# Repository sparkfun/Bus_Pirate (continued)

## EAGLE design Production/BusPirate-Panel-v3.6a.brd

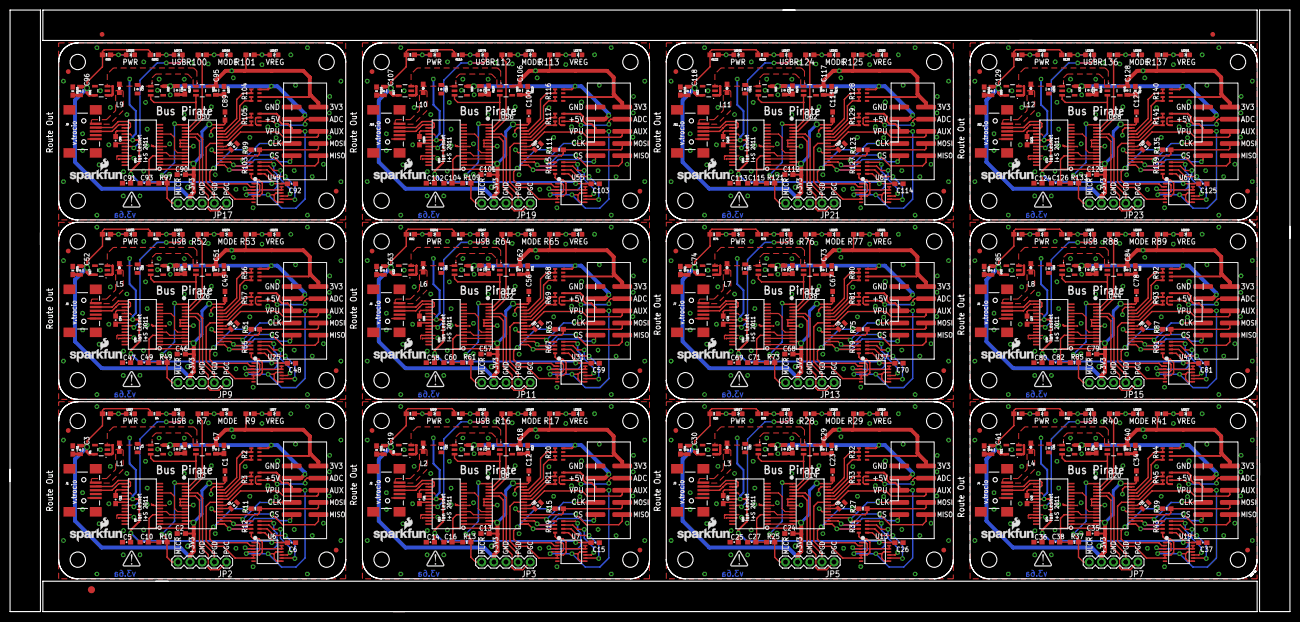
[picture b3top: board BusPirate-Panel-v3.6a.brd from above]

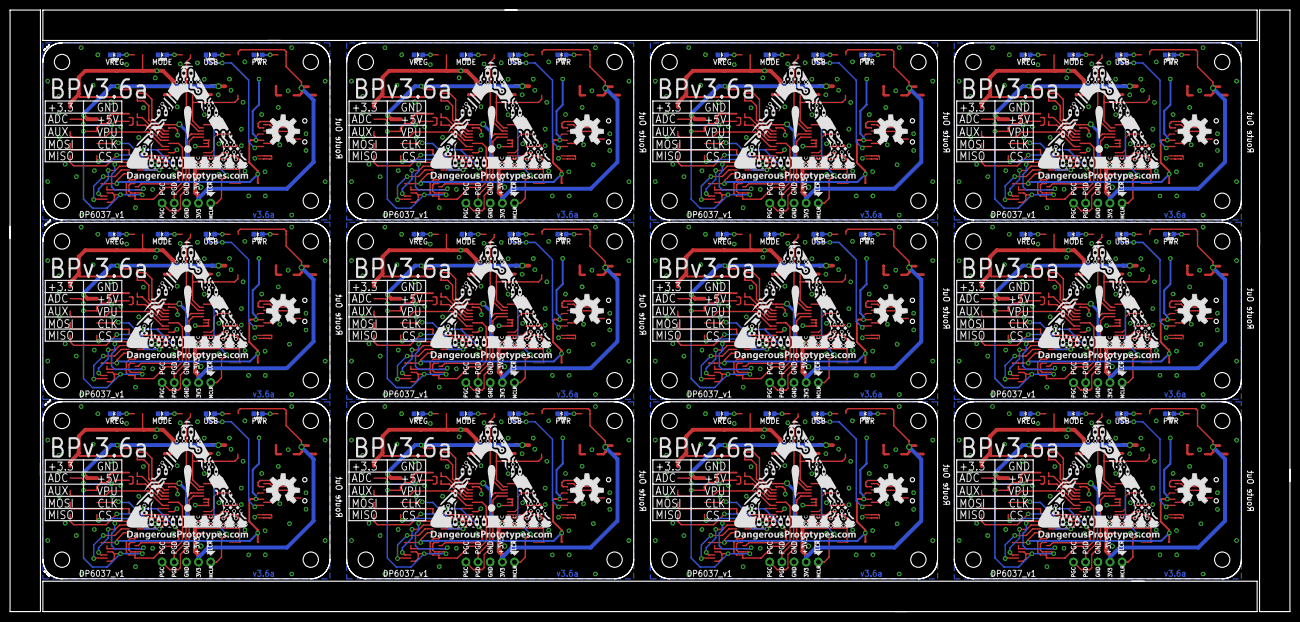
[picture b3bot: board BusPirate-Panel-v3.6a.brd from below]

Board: 2 copper layers, 267.5 x 125.7 mm, 579 parts (72 on the bottom side), 516 nets.

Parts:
C1, C2, C5, C6, C10, C11, C12, C13, C14, C15, C16, C21, C23, C24, C25, C26, C27, C32, C34, C35, C36, C37, C38, C43, C45, C46, C47, C48, C49, C54, C56, C57, C58, C59, C60, C65, C67, C68, C69, C70, C71, C76, C78, C79, C80, C81, C82, C87, C89, C90, C91, C92, C93, C98, C100, C101, C102, C103, C104, C109, C111, C112, C113, C114, C115, C120, C122, C123, C124, C125, C126, C131: 0.1uF; 0603-CAP
C3, C4, C7, C8, C9, C17, C18, C19, C20, C22, C28, C29, C30, C31, C33, C39, C40, C41, C42, C44, C50, C51, C52, C53, C55, C61, C62, C63, C64, C66, C72, C73, C74, C75, C77, C83, C84, C85, C86, C88, C94, C95, C96, C97, C99, C105, C106, C107, C108, C110, C116, C117, C118, C119, C121, C127, C128, C129, C130, C132: 10uF; 0805-CAP
E$1: FIDUCIAL-1.5X3
E$7, E$8: FIDUCIAL-1X2
FID1, FID2, FID3, FID4, FID5, FID6, FID7, FID8, FID9, FID10, FID11, FID12, FID13, FID14, FID15, FID16, FID17, FID18, FID19, FID20, FID21, FID22, FID23, FID24: FIDUCIAL1X2; FIDUCIAL-1X2
J1, J2, J3, J4, J5, J6, J7, J8, J9, J10, J11, J12: USB-MINIB-5PIN; USB-MINIB
JP1, JP4, JP6, JP8, JP10, JP12, JP14, JP16, JP18, JP20, JP22, JP24: 2X5-SHROUDED_SMD
JP2, JP3, JP5, JP7, JP9, JP11, JP13, JP15, JP17, JP19, JP21, JP23: 1X05
L1, L2, L3, L4, L5, L6, L7, L8, L9, L10, L11, L12: 1A Ferrite; 0603
LED1, LED3, LED5, LED7, LED9, LED10, LED11, LED15, LED17, LED18, LED19, LED23, LED25, LED26, LED27, LED31, LED33, LED34, LED35, LED39, LED41, LED42, LED43, LED47, LED49, LED50, LED51, LED55, LED57, LED58, LED59, LED63, LED65, LED66, LED67, LED71, LED73, LED74, LED75, LED79, LED81, LED82, LED83, LED87, LED89, LED90, LED91, LED95: RED; LED-0603
LED2, LED4, LED6, LED8, LED12, LED13, LED14, LED16, LED20, LED21, LED22, LED24, LED28, LED29, LED30, LED32, LED36, LED37, LED38, LED40, LED44, LED45, LED46, LED48, LED52, LED53, LED54, LED56, LED60, LED61, LED62, LED64, LED68, LED69, LED70, LED72, LED76, LED77, LED78, LED80, LED84, LED85, LED86, LED88, LED92, LED93, LED94, LED96: DNP; LED-0603
LOGO1, LOGO4, LOGO6, LOGO8, LOGO10, LOGO12, LOGO14, LOGO16, LOGO18, LOGO20, LOGO22, LOGO24: OSHW-LOGOL; OSHW-LOGO-L
LOGO2, LOGO3, LOGO5, LOGO7, LOGO9, LOGO11, LOGO13, LOGO15, LOGO17, LOGO19, LOGO21, LOGO23: SFE_LOGO_NAME_FLAME.1_INCH; SFE_LOGO_NAME_FLAME_.1
PCB1, PCB2, PCB3, PCB4, PCB5, PCB6, PCB7, PCB8, PCB9, PCB10, PCB11, PCB12: PCB_DP_RECTANGLE-37X60; DP6037_V1
R1, R5, R8, R22, R23, R24, R34, R35, R36, R46, R47, R48, R58, R59, R60, R70, R71, R72, R82, R83, R84, R94, R95, R96, R106, R107, R108, R118, R119, R120, R130, R131, R132, R142, R143, R144: 0; 0603
R2, R3, R12, R19, R20, R21, R31, R32, R33, R43, R44, R45, R55, R56, R57, R67, R68, R69, R79, R80, R81, R91, R92, R93, R103, R104, R105, R115, R116, R117, R127, R128, R129, R139, R140, R141: 10k; 4XARRAY
R4, R6, R7, R9, R14, R16, R17, R18, R26, R28, R29, R30, R38, R40, R41, R42, R50, R52, R53, R54, R62, R64, R65, R66, R74, R76, R77, R78, R86, R88, R89, R90, R98, R100, R101, R102, R110, R112, R113, R114, R122, R124, R125, R126, R134, R136, R137, R138: 1K; 0603-RES
R10, R11, R13, R15, R25, R27, R37, R39, R49, R51, R61, R63, R73, R75, R85, R87, R97, R99, R109, R111, R121, R123, R133, R135: 2.0k; 0603-RES
U1, U2, U9, U10, U15, U16, U21, U22, U27, U28, U33, U34, U39, U40, U45, U46, U51, U52, U57, U58, U63, U64, U69, U70: MIC5205 3V3; SOT23-5
U3, U8, U14, U20, U26, U32, U38, U44, U50, U56, U62, U68: PIC24FJ64GA002; SSOP28
U4, U11, U17, U23, U29, U35, U41, U47, U53, U59, U65, U71: MIC5205 5V0; SOT23-5
U5, U12, U18, U24, U30, U36, U42, U48, U54, U60, U66, U72: FT232RL-BASICSSOP; SSOP28DB
U6, U7, U13, U19, U25, U31, U37, U43, U49, U55, U61, U67: 4066; TSSOP14
U$1, U$2, U$5, U$7, U$9, U$11, U$13, U$15, U$17, U$19, U$21, U$23: DP-LOGO
U$3, U$4, U$6, U$8, U$10, U$12, U$14, U$16, U$18, U$20, U$22, U$24: DP_LOGO_ART_1X1

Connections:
5V: C4.1, C5.1, C6.1, L1.2, R12.5, U1.1, U1.3, U2.1, U4.1, U5.20, U6.14
5V1: C14.1, C15.1, C22.1, L2.2, R19.5, U7.14, U9.1, U9.3, U10.1, U11.1, U12.20
5V2: C25.1, C26.1, C33.1, L3.2, R31.5, U13.14, U15.1, U15.3, U16.1, U17.1, U18.20
5V3: C36.1, C37.1, C44.1, L4.2, R43.5, U19.14, U21.1, U21.3, U22.1, U23.1, U24.20
5V4: C47.1, C48.1, C55.1, L5.2, R55.5, U25.14, U27.1, U27.3, U28.1, U29.1, U30.20
5V5: C58.1, C59.1, C66.1, L6.2, R67.5, U31.14, U33.1, U33.3, U34.1, U35.1, U36.20
5V6: C69.1, C70.1, C77.1, L7.2, R79.5, U37.14, U39.1, U39.3, U40.1, U41.1, U42.20
5V7: C80.1, C81.1, C88.1, L8.2, R91.5, U43.14, U45.1, U45.3, U46.1, U47.1, U48.20
5V8: C91.1, C92.1, C99.1, L9.2, R103.5, U49.14, U51.1, U51.3, U52.1, U53.1, U54.20
5V9: C102.1, C103.1, C110.1, L10.2, R115.5, U55.14, U57.1, U57.3, U58.1, U59.1, U60.20
5V10: C113.1, C114.1, C121.1, L11.2, R127.5, U61.14, U63.1, U63.3, U64.1, U65.1, U66.20
5V11: C124.1, C125.1, C132.1, L12.2, R139.5, U67.14, U69.1, U69.3, U70.1, U71.1, U72.20
!MCLR: JP2.5, R10.1, U3.1
!MCLR1: JP3.5, R13.1, U8.1
!MCLR2: JP5.5, R25.1, U14.1
!MCLR3: JP7.5, R37.1, U20.1
!MCLR4: JP9.5, R49.1, U26.1
!MCLR5: JP11.5, R61.1, U32.1
!MCLR6: JP13.5, R73.1, U38.1
!MCLR7: JP15.5, R85.1, U44.1
!MCLR8: JP17.5, R97.1, U50.1
!MCLR9: JP19.5, R109.1, U56.1
!MCLR10: JP21.5, R121.1, U62.1
!MCLR11: JP23.5, R133.1, U68.1
$N1: J2.VBUS, L2.1
$N2: J3.VBUS, L3.1
$N3: J4.VBUS, L4.1
$N4: J5.VBUS, L5.1
$N5: J6.VBUS, L6.1
$N6: J7.VBUS, L7.1
$N7: J8.VBUS, L8.1
$N8: J9.VBUS, L9.1
$N9: J10.VBUS, L10.1
$N10: J11.VBUS, L11.1
$N11: J12.VBUS, L12.1
$N26: J1.VBUS, L1.1
ADC: JP1.4, R3.6
ADC1: R3.3, R3.4, U3.23
ADC2: R3.1, R3.2, U3.24
ADC3: R2.3, R2.4, U3.25
ADC4: R2.1, R2.2, U3.26
ADC5: R21.3, R21.4, U8.23
ADC6: JP4.4, R21.6
ADC7: R21.1, R21.2, U8.24
ADC8: R20.3, R20.4, U8.25
ADC9: R20.1, R20.2, U8.26
ADC10: R33.3, R33.4, U14.23
ADC11: JP6.4, R33.6
ADC12: R33.1, R33.2, U14.24
ADC13: R32.3, R32.4, U14.25
ADC14: R32.1, R32.2, U14.26
ADC15: R45.3, R45.4, U20.23
ADC16: JP8.4, R45.6
ADC17: R45.1, R45.2, U20.24
ADC18: R44.3, R44.4, U20.25
ADC19: R44.1, R44.2, U20.26
ADC20: R57.3, R57.4, U26.23
ADC21: JP10.4, R57.6
ADC22: R57.1, R57.2, U26.24
ADC23: R56.3, R56.4, U26.25
ADC24: R56.1, R56.2, U26.26
ADC25: R69.3, R69.4, U32.23
ADC26: JP12.4, R69.6
ADC27: R69.1, R69.2, U32.24
ADC28: R68.3, R68.4, U32.25
ADC29: R68.1, R68.2, U32.26
ADC30: R81.3, R81.4, U38.23
ADC31: JP14.4, R81.6
ADC32: R81.1, R81.2, U38.24
ADC33: R80.3, R80.4, U38.25
ADC34: R80.1, R80.2, U38.26
ADC35: R93.3, R93.4, U44.23
ADC36: JP16.4, R93.6
ADC37: R93.1, R93.2, U44.24
ADC38: R92.3, R92.4, U44.25
ADC39: R92.1, R92.2, U44.26
ADC40: R105.3, R105.4, U50.23
ADC41: JP18.4, R105.6
ADC42: R105.1, R105.2, U50.24
ADC43: R104.3, R104.4, U50.25
ADC44: R104.1, R104.2, U50.26
ADC45: R117.3, R117.4, U56.23
ADC46: JP20.4, R117.6
ADC47: R117.1, R117.2, U56.24
ADC48: R116.3, R116.4, U56.25
ADC49: R116.1, R116.2, U56.26
ADC50: R129.3, R129.4, U62.23
ADC51: JP22.4, R129.6
ADC52: R129.1, R129.2, U62.24
ADC53: R128.3, R128.4, U62.25
ADC54: R128.1, R128.2, U62.26
ADC55: R141.3, R141.4, U68.23
ADC56: JP24.4, R141.6
ADC57: R141.1, R141.2, U68.24
ADC58: R140.3, R140.4, U68.25
ADC59: R140.1, R140.2, U68.26
AUX1: JP1.6, U3.21
AUX2: JP4.6, U8.21
AUX3: JP6.6, U14.21
AUX4: JP8.6, U20.21
AUX5: JP10.6, U26.21
AUX6: JP12.6, U32.21
AUX7: JP14.6, U38.21
AUX8: JP16.6, U44.21
AUX9: JP18.6, U50.21
AUX10: JP20.6, U56.21
AUX11: JP22.6, U62.21
AUX12: JP24.6, U68.21
CLK: JP1.7, R12.1, U3.17
CLK1: JP4.7, R19.1, U8.17
CLK2: JP6.7, R31.1, U14.17
CLK3: JP8.7, R43.1, U20.17
CLK4: JP10.7, R55.1, U26.17
CLK5: JP12.7, R67.1, U32.17
CLK6: JP14.7, R79.1, U38.17
CLK7: JP16.7, R91.1, U44.17
CLK8: JP18.7, R103.1, U50.17
CLK9: JP20.7, R115.1, U56.17
CLK10: JP22.7, R127.1, U62.17
CLK11: JP24.7, R139.1, U68.17
CS: JP1.9, R12.3, U3.15
CS1: JP4.9, R19.3, U8.15
CS2: JP6.9, R31.3, U14.15
CS3: JP8.9, R43.3, U20.15
CS4: JP10.9, R55.3, U26.15
CS5: JP12.9, R67.3, U32.15
CS6: JP14.9, R79.3, U38.15
CS7: JP16.9, R91.3, U44.15
CS8: JP18.9, R103.3, U50.15
CS9: JP20.9, R115.3, U56.15
CS10: JP22.9, R127.3, U62.15
CS11: JP24.9, R139.3, U68.15
CTS: U3.10, U5.11
CTS1: U8.10, U12.11
CTS2: U14.10, U18.11
CTS3: U20.10, U24.11
CTS4: U26.10, U30.11
CTS5: U32.10, U36.11
CTS6: U38.10, U42.11
CTS7: U44.10, U48.11
CTS8: U50.10, U54.11
CTS9: U56.10, U60.11
CTS10: U62.10, U66.11
CTS11: U68.10, U72.11
D+: J1.D+, U5.15
D+1: J2.D+, U12.15
D+2: J3.D+, U18.15
D+3: J4.D+, U24.15
D+4: J5.D+, U30.15
D+5: J6.D+, U36.15
D+6: J7.D+, U42.15
D+7: J8.D+, U48.15
D+8: J9.D+, U54.15
D+9: J10.D+, U60.15
D+10: J11.D+, U66.15
D+11: J12.D+, U72.15
D-: J1.D-, U5.16
D-1: J2.D-, U12.16
D-2: J3.D-, U18.16
D-3: J4.D-, U24.16
D-4: J5.D-, U30.16
D-5: J6.D-, U36.16
D-6: J7.D-, U42.16
D-7: J8.D-, U48.16
D-8: J9.D-, U54.16
D-9: J10.D-, U60.16
D-10: J11.D-, U66.16
D-11: J12.D-, U72.16
GND: C1.2, C2.2, C4.2, C5.2, C6.2, C9.2, C10.2, C11.2, J1.GND, JP1.1, JP2.3, LED3.C, LED4.C, LED5.C, LED6.C, LED7.C, LED8.C, R1.1, R2.5, R2.7, R3.5, R3.7, R5.1, R8.1, U1.2, U2.2, U3.6, U3.7, U3.8, U3.19, U3.27, U4.2, U5.7, U5.18, U5.21, U5.25, U5.26, U6.7
GND1: C12.2, C13.2, C14.2, C15.2, C16.2, C20.2, C21.2, C22.2, J2.GND, JP3.3, JP4.1, LED9.C, LED10.C, LED11.C, LED12.C, LED13.C, LED14.C, R20.5, R20.7, R21.5, R21.7, R22.1, R23.1, R24.1, U7.7, U8.6, U8.7, U8.8, U8.19, U8.27, U9.2, U10.2, U11.2, U12.7, U12.18, U12.21, U12.25, U12.26
GND2: C23.2, C24.2, C25.2, C26.2, C27.2, C31.2, C32.2, C33.2, J3.GND, JP5.3, JP6.1, LED17.C, LED18.C, LED19.C, LED20.C, LED21.C, LED22.C, R32.5, R32.7, R33.5, R33.7, R34.1, R35.1, R36.1, U13.7, U14.6, U14.7, U14.8, U14.19, U14.27, U15.2, U16.2, U17.2, U18.7, U18.18, U18.21, U18.25, U18.26
GND3: C34.2, C35.2, C36.2, C37.2, C38.2, C42.2, C43.2, C44.2, J4.GND, JP7.3, JP8.1, LED25.C, LED26.C, LED27.C, LED28.C, LED29.C, LED30.C, R44.5, R44.7, R45.5, R45.7, R46.1, R47.1, R48.1, U19.7, U20.6, U20.7, U20.8, U20.19, U20.27, U21.2, U22.2, U23.2, U24.7, U24.18, U24.21, U24.25, U24.26
GND4: C45.2, C46.2, C47.2, C48.2, C49.2, C53.2, C54.2, C55.2, J5.GND, JP9.3, JP10.1, LED33.C, LED34.C, LED35.C, LED36.C, LED37.C, LED38.C, R56.5, R56.7, R57.5, R57.7, R58.1, R59.1, R60.1, U25.7, U26.6, U26.7, U26.8, U26.19, U26.27, U27.2, U28.2, U29.2, U30.7, U30.18, U30.21, U30.25, U30.26
GND5: C56.2, C57.2, C58.2, C59.2, C60.2, C64.2, C65.2, C66.2, J6.GND, JP11.3, JP12.1, LED41.C, LED42.C, LED43.C, LED44.C, LED45.C, LED46.C, R68.5, R68.7, R69.5, R69.7, R70.1, R71.1, R72.1, U31.7, U32.6, U32.7, U32.8, U32.19, U32.27, U33.2, U34.2, U35.2, U36.7, U36.18, U36.21, U36.25, U36.26
GND6: C67.2, C68.2, C69.2, C70.2, C71.2, C75.2, C76.2, C77.2, J7.GND, JP13.3, JP14.1, LED49.C, LED50.C, LED51.C, LED52.C, LED53.C, LED54.C, R80.5, R80.7, R81.5, R81.7, R82.1, R83.1, R84.1, U37.7, U38.6, U38.7, U38.8, U38.19, U38.27, U39.2, U40.2, U41.2, U42.7, U42.18, U42.21, U42.25, U42.26
GND7: C78.2, C79.2, C80.2, C81.2, C82.2, C86.2, C87.2, C88.2, J8.GND, JP15.3, JP16.1, LED57.C, LED58.C, LED59.C, LED60.C, LED61.C, LED62.C, R92.5, R92.7, R93.5, R93.7, R94.1, R95.1, R96.1, U43.7, U44.6, U44.7, U44.8, U44.19, U44.27, U45.2, U46.2, U47.2, U48.7, U48.18, U48.21, U48.25, U48.26
GND8: C89.2, C90.2, C91.2, C92.2, C93.2, C97.2, C98.2, C99.2, J9.GND, JP17.3, JP18.1, LED65.C, LED66.C, LED67.C, LED68.C, LED69.C, LED70.C, R104.5, R104.7, R105.5, R105.7, R106.1, R107.1, R108.1, U49.7, U50.6, U50.7, U50.8, U50.19, U50.27, U51.2, U52.2, U53.2, U54.7, U54.18, U54.21, U54.25, U54.26
GND9: C100.2, C101.2, C102.2, C103.2, C104.2, C108.2, C109.2, C110.2, J10.GND, JP19.3, JP20.1, LED73.C, LED74.C, LED75.C, LED76.C, LED77.C, LED78.C, R116.5, R116.7, R117.5, R117.7, R118.1, R119.1, R120.1, U55.7, U56.6, U56.7, U56.8, U56.19, U56.27, U57.2, U58.2, U59.2, U60.7, U60.18, U60.21, U60.25, U60.26
GND10: C111.2, C112.2, C113.2, C114.2, C115.2, C119.2, C120.2, C121.2, J11.GND, JP21.3, JP22.1, LED81.C, LED82.C, LED83.C, LED84.C, LED85.C, LED86.C, R128.5, R128.7, R129.5, R129.7, R130.1, R131.1, R132.1, U61.7, U62.6, U62.7, U62.8, U62.19, U62.27, U63.2, U64.2, U65.2, U66.7, U66.18, U66.21, U66.25, U66.26
GND11: C122.2, C123.2, C124.2, C125.2, C126.2, C130.2, C131.2, C132.2, J12.GND, JP23.3, JP24.1, LED89.C, LED90.C, LED91.C, LED92.C, LED93.C, LED94.C, R140.5, R140.7, R141.5, R141.7, R142.1, R143.1, R144.1, U67.7, U68.6, U68.7, U68.8, U68.19, U68.27, U69.2, U70.2, U71.2, U72.7, U72.18, U72.21, U72.25, U72.26
LD1: R7.2, U3.3
LD2: R16.2, U8.3
LD3: R28.2, U14.3
LD4: R40.2, U20.3
LD5: R52.2, U26.3
LD6: R64.2, U32.3
LD7: R76.2, U38.3
LD8: R88.2, U44.3
LD9: R100.2, U50.3
LD10: R112.2, U56.3
LD11: R124.2, U62.3
LD12: R136.2, U68.3
MISO: JP1.10, R12.2, U3.16
MISO1: JP4.10, R19.2, U8.16
MISO2: JP6.10, R31.2, U14.16
MISO3: JP8.10, R43.2, U20.16
MISO4: JP10.10, R55.2, U26.16
MISO5: JP12.10, R67.2, U32.16
MISO6: JP14.10, R79.2, U38.16
MISO7: JP16.10, R91.2, U44.16
MISO8: JP18.10, R103.2, U50.16
MISO9: JP20.10, R115.2, U56.16
MISO10: JP22.10, R127.2, U62.16
MISO11: JP24.10, R139.2, U68.16
MOSI: JP1.8, R11.1, U3.18
MOSI1: JP4.8, R15.1, U8.18
MOSI2: JP6.8, R27.1, U14.18
MOSI3: JP8.8, R39.1, U20.18
MOSI4: JP10.8, R51.1, U26.18
MOSI5: JP12.8, R63.1, U32.18
MOSI6: JP14.8, R75.1, U38.18
MOSI7: JP16.8, R87.1, U44.18
MOSI8: JP18.8, R99.1, U50.18
MOSI9: JP20.8, R111.1, U56.18
MOSI10: JP22.8, R123.1, U62.18
MOSI11: JP24.8, R135.1, U68.18
unnamed: R11.2, U6.2
unnamed: R12.6, U6.9
unnamed: C9.1, U3.20
unnamed: R12.7, U6.10
unnamed: R12.8, U6.3
unnamed: LED5.A, LED6.A, R7.1
unnamed: LED3.A, LED4.A, R6.1
unnamed: C3.2, R1.2
unnamed: C11.1, U5.17
unnamed: C7.2, R5.2
unnamed: C8.2, R8.2
unnamed: LED9.A, LED14.A, R14.1
unnamed: LED1.A, LED2.A, R4.1
unnamed: C20.1, U8.20
unnamed: LED10.A, LED13.A, R16.1
unnamed: LED11.A, LED12.A, R17.1
unnamed: R15.2, U7.2
unnamed: LED7.A, LED8.A, R9.1
unnamed: LED15.A, LED16.A, R18.1
unnamed: C21.1, U12.17
unnamed: R19.8, U7.3
unnamed: R19.6, U7.9
unnamed: R19.7, U7.10
unnamed: C19.2, R22.2
unnamed: C18.2, R23.2
unnamed: C17.2, R24.2
unnamed: LED17.A, LED22.A, R26.1
unnamed: C31.1, U14.20
unnamed: LED18.A, LED21.A, R28.1
unnamed: LED19.A, LED20.A, R29.1
unnamed: R27.2, U13.2
unnamed: LED23.A, LED24.A, R30.1
unnamed: C32.1, U18.17
unnamed: R31.8, U13.3
unnamed: R31.6, U13.9
unnamed: R31.7, U13.10
unnamed: C30.2, R34.2
unnamed: C29.2, R35.2
unnamed: C28.2, R36.2
unnamed: LED25.A, LED30.A, R38.1
unnamed: C42.1, U20.20
unnamed: LED26.A, LED29.A, R40.1
unnamed: LED27.A, LED28.A, R41.1
unnamed: R39.2, U19.2
unnamed: LED31.A, LED32.A, R42.1
unnamed: C43.1, U24.17
unnamed: R43.8, U19.3
unnamed: R43.6, U19.9
unnamed: R43.7, U19.10
unnamed: C41.2, R46.2
unnamed: C40.2, R47.2
unnamed: C39.2, R48.2
unnamed: LED33.A, LED38.A, R50.1
unnamed: C53.1, U26.20
unnamed: LED34.A, LED37.A, R52.1
unnamed: LED35.A, LED36.A, R53.1
unnamed: R51.2, U25.2
unnamed: LED39.A, LED40.A, R54.1
unnamed: C54.1, U30.17
unnamed: R55.8, U25.3
unnamed: R55.6, U25.9
unnamed: R55.7, U25.10
unnamed: C52.2, R58.2
unnamed: C51.2, R59.2
unnamed: C50.2, R60.2
unnamed: LED41.A, LED46.A, R62.1
unnamed: C64.1, U32.20
unnamed: LED42.A, LED45.A, R64.1
unnamed: LED43.A, LED44.A, R65.1
unnamed: R63.2, U31.2
unnamed: LED47.A, LED48.A, R66.1
unnamed: C65.1, U36.17
unnamed: R67.8, U31.3
unnamed: R67.6, U31.9
unnamed: R67.7, U31.10
unnamed: C63.2, R70.2
unnamed: C62.2, R71.2
unnamed: C61.2, R72.2
unnamed: LED49.A, LED54.A, R74.1
unnamed: C75.1, U38.20
unnamed: LED50.A, LED53.A, R76.1
unnamed: LED51.A, LED52.A, R77.1
unnamed: R75.2, U37.2
unnamed: LED55.A, LED56.A, R78.1
unnamed: C76.1, U42.17
unnamed: R79.8, U37.3
unnamed: R79.6, U37.9
unnamed: R79.7, U37.10
unnamed: C74.2, R82.2
unnamed: C73.2, R83.2
unnamed: C72.2, R84.2
unnamed: LED57.A, LED62.A, R86.1
unnamed: C86.1, U44.20
unnamed: LED58.A, LED61.A, R88.1
unnamed: LED59.A, LED60.A, R89.1
unnamed: R87.2, U43.2
unnamed: LED63.A, LED64.A, R90.1
unnamed: C87.1, U48.17
unnamed: R91.8, U43.3
unnamed: R91.6, U43.9
unnamed: R91.7, U43.10
unnamed: C85.2, R94.2
unnamed: C84.2, R95.2
unnamed: C83.2, R96.2
unnamed: LED65.A, LED70.A, R98.1
unnamed: C97.1, U50.20
unnamed: LED66.A, LED69.A, R100.1
unnamed: LED67.A, LED68.A, R101.1
unnamed: R99.2, U49.2
unnamed: LED71.A, LED72.A, R102.1
unnamed: C98.1, U54.17
unnamed: R103.8, U49.3
unnamed: R103.6, U49.9
unnamed: R103.7, U49.10
unnamed: C96.2, R106.2
unnamed: C95.2, R107.2
unnamed: C94.2, R108.2
unnamed: LED73.A, LED78.A, R110.1
unnamed: C108.1, U56.20
unnamed: LED74.A, LED77.A, R112.1
unnamed: LED75.A, LED76.A, R113.1
unnamed: R111.2, U55.2
unnamed: LED79.A, LED80.A, R114.1
unnamed: C109.1, U60.17
unnamed: R115.8, U55.3
unnamed: R115.6, U55.9
unnamed: R115.7, U55.10
unnamed: C107.2, R118.2
unnamed: C106.2, R119.2
unnamed: C105.2, R120.2
unnamed: LED81.A, LED86.A, R122.1
unnamed: C119.1, U62.20
unnamed: LED82.A, LED85.A, R124.1
unnamed: LED83.A, LED84.A, R125.1
unnamed: R123.2, U61.2
unnamed: LED87.A, LED88.A, R126.1
unnamed: C120.1, U66.17
unnamed: R127.8, U61.3
unnamed: R127.6, U61.9
unnamed: R127.7, U61.10
unnamed: C118.2, R130.2
unnamed: C117.2, R131.2
unnamed: C116.2, R132.2
unnamed: LED89.A, LED94.A, R134.1
unnamed: C130.1, U68.20
unnamed: LED90.A, LED93.A, R136.1
unnamed: LED91.A, LED92.A, R137.1
unnamed: R135.2, U67.2
unnamed: LED95.A, LED96.A, R138.1
unnamed: C131.1, U72.17
unnamed: R139.8, U67.3
unnamed: R139.6, U67.9
unnamed: R139.7, U67.10
unnamed: C129.2, R142.2
unnamed: C128.2, R143.2
unnamed: C127.2, R144.2
PGC: JP2.1, U3.5
PGC1: JP3.1, U8.5
PGC2: JP5.1, U14.5
PGC3: JP7.1, U20.5
PGC4: JP9.1, U26.5
PGC5: JP11.1, U32.5
PGC6: JP13.1, U38.5
PGC7: JP15.1, U44.5
PGC8: JP17.1, U50.5
PGC9: JP19.1, U56.5
PGC10: JP21.1, U62.5
PGC11: JP23.1, U68.5
PGD: JP2.2, U3.4
PGD1: JP3.2, U8.4
PGD2: JP5.2, U14.4
PGD3: JP7.2, U20.4
PGD4: JP9.2, U26.4
PGD5: JP11.2, U32.4
PGD6: JP13.2, U38.4
PGD7: JP15.2, U44.4
PGD8: JP17.2, U50.4
PGD9: JP19.2, U56.4
PGD10: JP21.2, U62.4
PGD11: JP23.2, U68.4
PULLUPEN: R12.4, U3.22, U6.5, U6.6, U6.12, U6.13
PULLUPEN1: R19.4, U7.5, U7.6, U7.12, U7.13, U8.22
PULLUPEN2: R31.4, U13.5, U13.6, U13.12, U13.13, U14.22
PULLUPEN3: R43.4, U19.5, U19.6, U19.12, U19.13, U20.22
PULLUPEN4: R55.4, U25.5, U25.6, U25.12, U25.13, U26.22
PULLUPEN5: R67.4, U31.5, U31.6, U31.12, U31.13, U32.22
PULLUPEN6: R79.4, U37.5, U37.6, U37.12, U37.13, U38.22
PULLUPEN7: R91.4, U43.5, U43.6, U43.12, U43.13, U44.22
PULLUPEN8: R103.4, U49.5, U49.6, U49.12, U49.13, U50.22
PULLUPEN9: R115.4, U55.5, U55.6, U55.12, U55.13, U56.22
PULLUPEN10: R127.4, U61.5, U61.6, U61.12, U61.13, U62.22
PULLUPEN11: R139.4, U67.5, U67.6, U67.12, U67.13, U68.22
RTS: U3.12, U5.3
RTS1: U8.12, U12.3
RTS2: U14.12, U18.3
RTS3: U20.12, U24.3
RTS4: U26.12, U30.3
RTS5: U32.12, U36.3
RTS6: U38.12, U42.3
RTS7: U44.12, U48.3
RTS8: U50.12, U54.3
RTS9: U56.12, U60.3
RTS10: U62.12, U66.3
RTS11: U68.12, U72.3
RX: U3.11, U5.5
RX1: U8.11, U12.5
RX2: U14.11, U18.5
RX3: U20.11, U24.5
RX4: U26.11, U30.5
RX5: U32.11, U36.5
RX6: U38.11, U42.5
RX7: U44.11, U48.5
RX8: U50.11, U54.5
RX9: U56.11, U60.5
RX10: U62.11, U66.5
RX11: U68.11, U72.5
RXLED: LED1.C, LED2.C, U5.22
RXLED1: LED15.C, LED16.C, U12.22
RXLED2: LED23.C, LED24.C, U18.22
RXLED3: LED31.C, LED32.C, U24.22
RXLED4: LED39.C, LED40.C, U30.22
RXLED5: LED47.C, LED48.C, U36.22
RXLED6: LED55.C, LED56.C, U42.22
RXLED7: LED63.C, LED64.C, U48.22
RXLED8: LED71.C, LED72.C, U54.22
RXLED9: LED79.C, LED80.C, U60.22
RXLED10: LED87.C, LED88.C, U66.22
RXLED11: LED95.C, LED96.C, U72.22
SW3V1: C18.1, JP4.2, R17.2, R20.6, U10.5
SW3V2: C29.1, JP6.2, R29.2, R32.6, U16.5
SW3V3: C7.1, JP1.2, R2.6, R9.2, U2.5
SW3V4: C40.1, JP8.2, R41.2, R44.6, U22.5
SW3V5: C51.1, JP10.2, R53.2, R56.6, U28.5
SW3V6: C62.1, JP12.2, R65.2, R68.6, U34.5
SW3V7: C73.1, JP14.2, R77.2, R80.6, U40.5
SW3V8: C84.1, JP16.2, R89.2, R92.6, U46.5
SW3V9: C95.1, JP18.2, R101.2, R104.6, U52.5
SW3V10: C106.1, JP20.2, R113.2, R116.6, U58.5
SW3V11: C117.1, JP22.2, R125.2, R128.6, U64.5
SW3V12: C128.1, JP24.2, R137.2, R140.6, U70.5
SW5V0: C8.1, JP1.3, R2.8, U4.5
SW5V1: C17.1, JP4.3, R20.8, U11.5
SW5V2: C28.1, JP6.3, R32.8, U17.5
SW5V3: C39.1, JP8.3, R44.8, U23.5
SW5V4: C50.1, JP10.3, R56.8, U29.5
SW5V5: C61.1, JP12.3, R68.8, U35.5
SW5V6: C72.1, JP14.3, R80.8, U41.5
SW5V7: C83.1, JP16.3, R92.8, U47.5
SW5V8: C94.1, JP18.3, R104.8, U53.5
SW5V9: C105.1, JP20.3, R116.8, U59.5
SW5V10: C116.1, JP22.3, R128.8, U65.5
SW5V11: C127.1, JP24.3, R140.8, U71.5
TX: U3.14, U5.1
TX1: U8.14, U12.1
TX2: U14.14, U18.1
TX3: U20.14, U24.1
TX4: U26.14, U30.1
TX5: U32.14, U36.1
TX6: U38.14, U42.1
TX7: U44.14, U48.1
TX8: U50.14, U54.1
TX9: U56.14, U60.1
TX10: U62.14, U66.1
TX11: U68.14, U72.1
VCC: C1.1, C2.1, C3.1, C10.1, JP2.4, R4.2, R6.2, R10.2, U1.5, U3.13, U3.28, U5.4
VCC1: C12.1, C13.1, C16.1, C19.1, JP3.4, R13.2, R14.2, R18.2, U8.13, U8.28, U9.5, U12.4
VCC2: C23.1, C24.1, C27.1, C30.1, JP5.4, R25.2, R26.2, R30.2, U14.13, U14.28, U15.5, U18.4
VCC3: C34.1, C35.1, C38.1, C41.1, JP7.4, R37.2, R38.2, R42.2, U20.13, U20.28, U21.5, U24.4
VCC4: C45.1, C46.1, C49.1, C52.1, JP9.4, R49.2, R50.2, R54.2, U26.13, U26.28, U27.5, U30.4
VCC5: C56.1, C57.1, C60.1, C63.1, JP11.4, R61.2, R62.2, R66.2, U32.13, U32.28, U33.5, U36.4
VCC6: C67.1, C68.1, C71.1, C74.1, JP13.4, R73.2, R74.2, R78.2, U38.13, U38.28, U39.5, U42.4
VCC7: C78.1, C79.1, C82.1, C85.1, JP15.4, R85.2, R86.2, R90.2, U44.13, U44.28, U45.5, U48.4
VCC8: C89.1, C90.1, C93.1, C96.1, JP17.4, R97.2, R98.2, R102.2, U50.13, U50.28, U51.5, U54.4
VCC9: C100.1, C101.1, C104.1, C107.1, JP19.4, R109.2, R110.2, R114.2, U56.13, U56.28, U57.5, U60.4
VCC10: C111.1, C112.1, C115.1, C118.1, JP21.4, R121.2, R122.2, R126.2, U62.13, U62.28, U63.5, U66.4
VCC11: C122.1, C123.1, C126.1, C129.1, JP23.4, R133.2, R134.2, R138.2, U68.13, U68.28, U69.5, U72.4
VEXTERN: JP1.5, R3.8, U6.1, U6.4, U6.8, U6.11
VEXTERN1: JP4.5, R21.8, U7.1, U7.4, U7.8, U7.11
VEXTERN2: JP6.5, R33.8, U13.1, U13.4, U13.8, U13.11
VEXTERN3: JP8.5, R45.8, U19.1, U19.4, U19.8, U19.11
VEXTERN4: JP10.5, R57.8, U25.1, U25.4, U25.8, U25.11
VEXTERN5: JP12.5, R69.8, U31.1, U31.4, U31.8, U31.11
VEXTERN6: JP14.5, R81.8, U37.1, U37.4, U37.8, U37.11
VEXTERN7: JP16.5, R93.8, U43.1, U43.4, U43.8, U43.11
VEXTERN8: JP18.5, R105.8, U49.1, U49.4, U49.8, U49.11
VEXTERN9: JP20.5, R117.8, U55.1, U55.4, U55.8, U55.11
VEXTERN10: JP22.5, R129.8, U61.1, U61.4, U61.8, U61.11
VEXTERN11: JP24.5, R141.8, U67.1, U67.4, U67.8, U67.11
VREGEN: U2.3, U3.2, U4.3
VREGEN1: U8.2, U10.3, U11.3
VREGEN2: U14.2, U16.3, U17.3
VREGEN3: U20.2, U22.3, U23.3
VREGEN4: U26.2, U28.3, U29.3
VREGEN5: U32.2, U34.3, U35.3
VREGEN6: U38.2, U40.3, U41.3
VREGEN7: U44.2, U46.3, U47.3
VREGEN8: U50.2, U52.3, U53.3
VREGEN9: U56.2, U58.3, U59.3
VREGEN10: U62.2, U64.3, U65.3
VREGEN11: U68.2, U70.3, U71.3

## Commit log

2014-02-06 Initial file commit
2015-09-15 First commit of v3.6a
2015-09-17 Finished inital DFM
2015-09-21 Changed from SFE to DP versioning, and changed bottom LEDs to DNP
2015-09-21 Changed license from CC4 to CC0
2015-09-23 Addressed issues
2015-10-08 Imported DP PCB part, and changed DRC to allow mask to cover large vias.
2015-11-09 Changed one PROD_ID and version number
2015-11-18 created panel v3.6a
2016-01-12 Corrected resistor value
2016-02-10 Added license info, and fixed up the README
2016-02-10 Update README.md
    Fixed formatting.
2016-02-11 MINOR format change
2019-02-04 Update link to v36
    Our version now has a "retired" link
